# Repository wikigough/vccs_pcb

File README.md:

# Design
## Aims
 - The primary aim of this design was to make a tool for the lab for various testing purposes, which is why there are multiple current modes for the sink.
 - The secondary aim was to experiment with image printing on PCBs and learn how to use Inkscape!

## Design details
The design is a simple voltage controlled current sink. The simulation for the LTSpice circuit simualtion is stored in `\sims`. 
In a nutshell, the sink is controlled by applying 0-1V into the VCONTROL input, either into the SMA connector or the right angled header. 
The `SINK_SELECTx` setting maps the 0-1V voltage input to one of either: 0-3A, 0-1A, 0-100mA, 0-10mA or 0-1mA.
_For inductive loads, please control the slew rate into the VCONTROL input, or adjust the initial passive RC filter from the VCONTROL input, otherwise the control loop may oscillate._

### Image vs silkscreen
 Please note, although there is silkscreen in the KiCAD project, the silkscreen was not generated as a manufacturing output, and was only used as a guide for the image in inkscape. 
 Both silkscreen *and* image printing are allowed, where silkscreen can be applied after the image printing. In hindsight, this combination could've been used.  

### External Control
A right-angled header was put into the design, so that the circuit can be controlled by an external microcontroller. 

## Library
The parts used in the library are stored in a different repo. For passives, the approach of using generic parts and filling them into the schematic was taken. 

# Using the PCBA

## Sink select lines
*One* of the `SINK_SELECTx` lines must be set, either on the board with the onboard DIP switch or by applying voltage on the external header. Please ensure all the DIP switch is all off before plugging in an external controller! Please note that only *one* line is allowed to be set - otherwise you will parallelise sense resistors, unless that is what is wanted.

## Voltage control input
The sink is controlled by inputting a 0-1V voltage waveform into VCONTROL. The voltage can be arbitrary. 

## Fan
For higher power dissipations, a fan must be mounted against the PCB to cool the DPAK transistor, which is the main dissipator of power.

# Data generation and ordering
## Kicad output data generation
Although used PCBWay, used these settings for generating the data output:
https://jlcpcb.com/help/article/how-to-generate-gerber-and-drill-files-in-kicad-9
The size came out as correct in the order page.

## Instructions for ordering
The order screenshots are shown in `\vccs\pcbway_order`.
The png files uploaded are in `\vccs\art\final_images`.
The following guide was used: 
 - https://www.pcbway.com/blog/News/Unlock_Color_PCB_Printing_with_PCBWay_0939d559.html
 - https://www.pcbway.com/project/question/KiCAD_and_Multicolor_Silkscreen.html

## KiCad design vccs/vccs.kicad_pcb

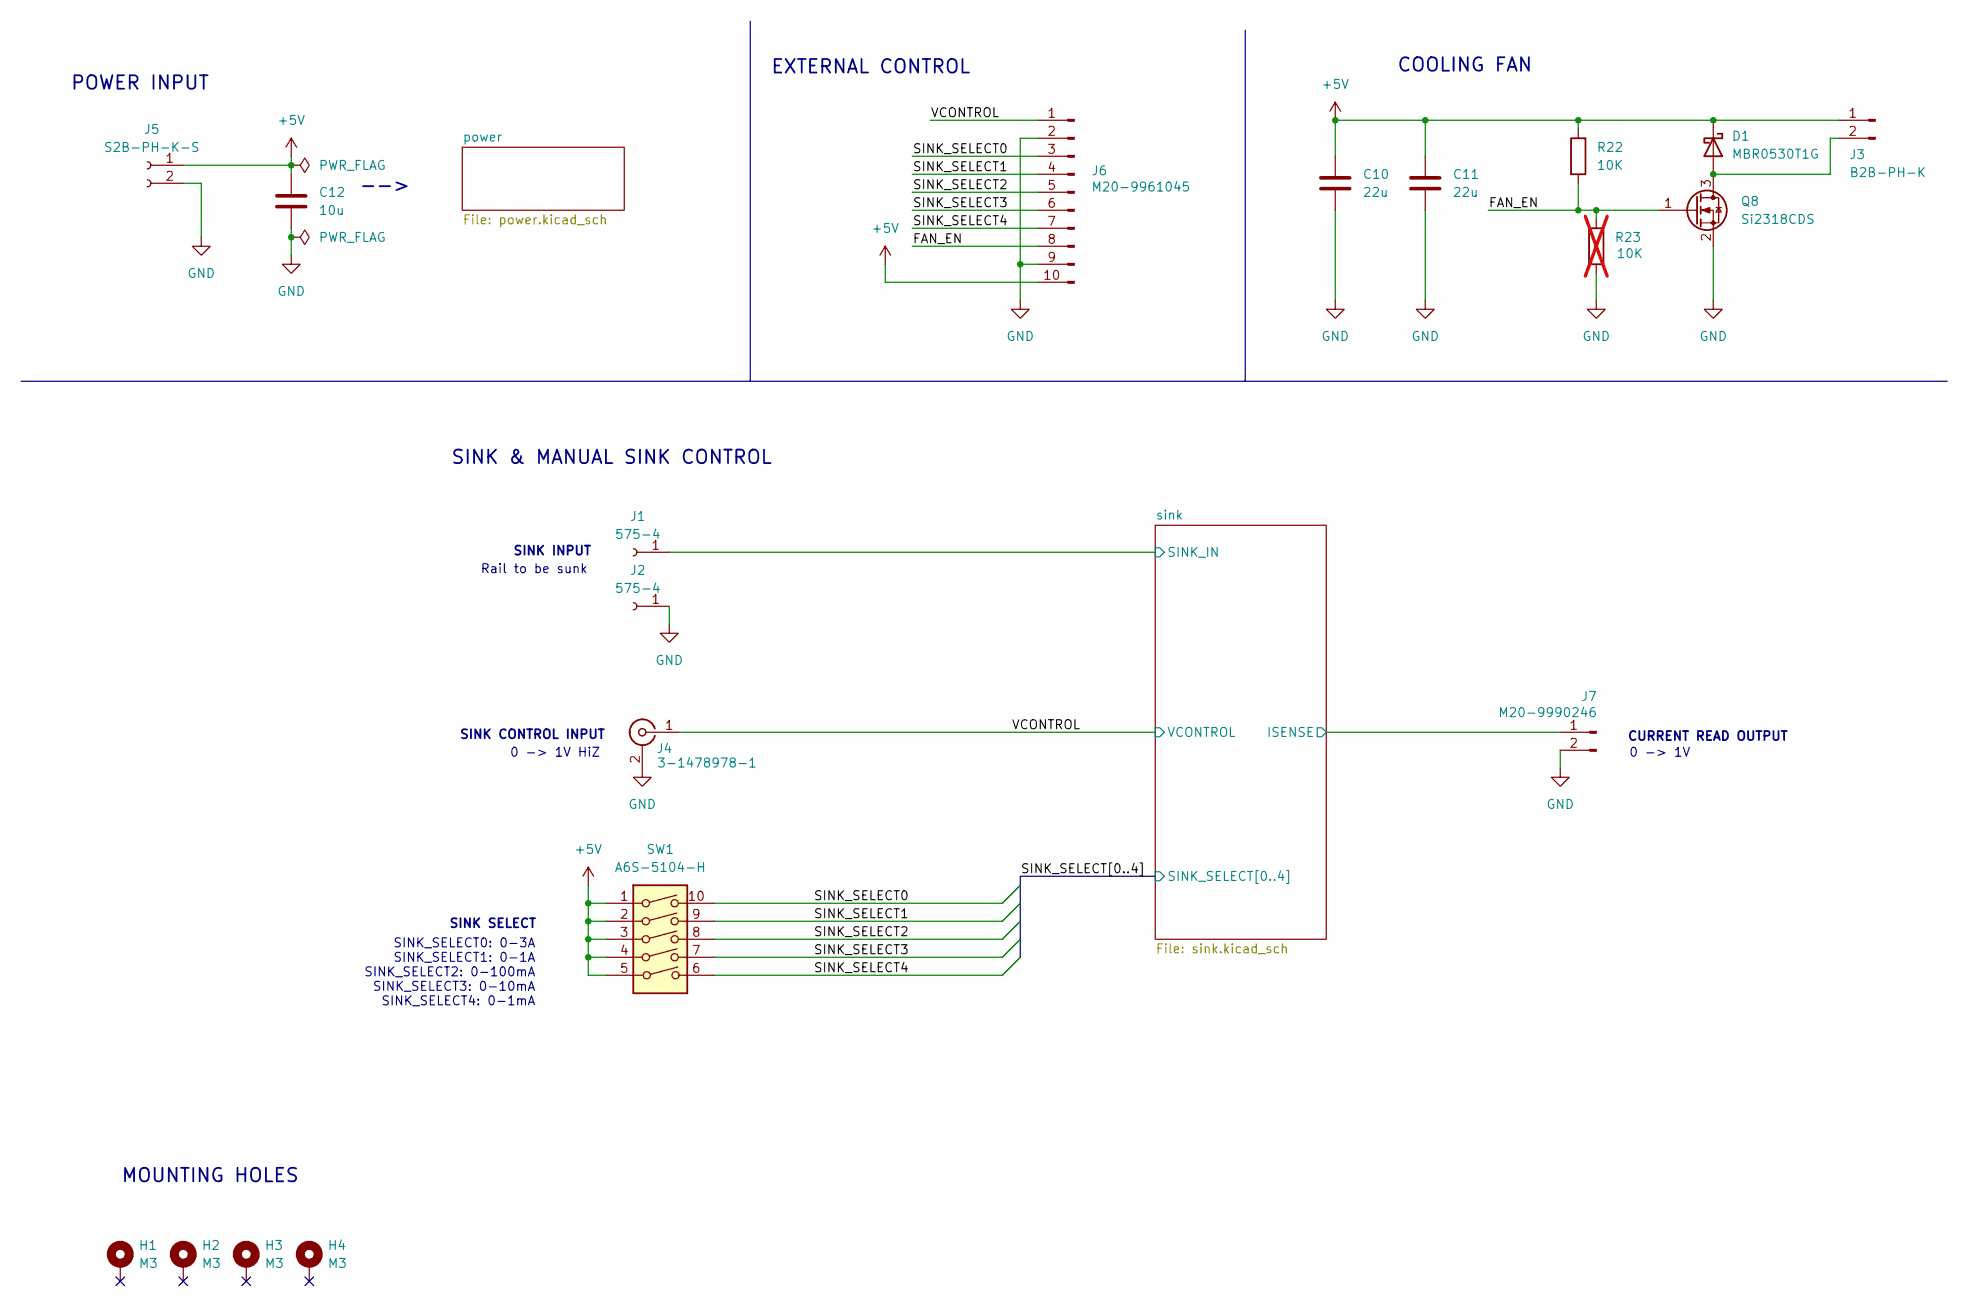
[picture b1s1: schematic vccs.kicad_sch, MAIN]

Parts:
C10, C11: 22u; C_1210_3225Metric_Pad1.33x2.70mm_HandSolder; Voltage Rating 16V; Tolerance 20%; MPN CL32A226MOJNNNE
C12: 10u; C_0805_2012Metric; Voltage Rating 16V; MPN GRM21BZ71C106KE15L
D1: MBR0530T1G; D_SOD-123; MPN MBR0530T1G
H1, H2, H3, H4: M3; MountingHole_3.2mm_M3_Pad_Via
J1, J2: 575-4; MPN 575-4
J3: B2B-PH-K; JST_PH_B2B-PH-K_1x02_P2.00mm_Vertical; MPN B2B-PH-K
J4: 3-1478978-1; MPN 3-1478978-1
J5: S2B-PH-K-S; JST_PH_S2B-PH-K_1x02_P2.00mm_Horizontal; MPN S2B-PH-K-S
J6: M20-9961045; PinHeader_1x10_P2.54mm_Horizontal; MPN M20-9961045
J7: M20-9990246; PinHeader_1x02_P2.54mm_Vertical; MPN M20-9990246
Q8: Si2318CDS; SOT-23-3; MPN SI2318CDS-T1-BE3
R22: 10K; R_0603_1608Metric; Tolerance 1%; Power Rating 1/10W; MPN RC0603FR-0710KL
R23: 10K; R_0603_1608Metric; Tolerance 1%; Power Rating 1/10W; MPN RC0603FR-0710KL; not fitted
SW1: A6S-5104-H; MPN A6S-5104-H

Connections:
+5V: C10.1, C11.1, C12.1, D1.1 (K), J3.1, J5.1, J6.10, R22.1, SW1.1, SW1.2, SW1.3, SW1.4, SW1.5; also elsewhere on the board
/FAN_EN: J6.8, Q8.1 (G), R22.2, R23.1
/SINK_SELECT0: J6.3, SW1.10; also elsewhere on the board
/SINK_SELECT1: J6.4, SW1.9; also elsewhere on the board
/SINK_SELECT2: J6.5, SW1.8; also elsewhere on the board
/SINK_SELECT3: J6.6, SW1.7; also elsewhere on the board
/SINK_SELECT4: J6.7, SW1.6; also elsewhere on the board
/VCONTROL: J4.1 (In), J6.1; also elsewhere on the board
/sink/ISENSE: J7.1; also elsewhere on the board
/sink/SINK_IN: J1.1; also elsewhere on the board
GND: C10.2, C11.2, C12.2, J2.1, J4.2 (Ext), J5.2, J6.2, J6.9, J7.2, Q8.2 (S), R23.2; also elsewhere on the board
unnamed: D1.2 (A), J3.2, Q8.3 (D)

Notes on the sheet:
Rail to be sunk
0 -> 1V HiZ
-->
SINK & MANUAL SINK CONTROL
0 -> 1V
EXTERNAL CONTROL
COOLING FAN
SINK_SELECT0: 0-3A SINK_SELECT1: 0-1A SINK_SELECT2: 0-100mA SINK_SELECT3: 0-10mA SINK_SELECT4: 0-1mA
CURRENT READ OUTPUT
SINK SELECT
SINK CONTROL INPUT
SINK INPUT
MOUNTING HOLES
POWER INPUT

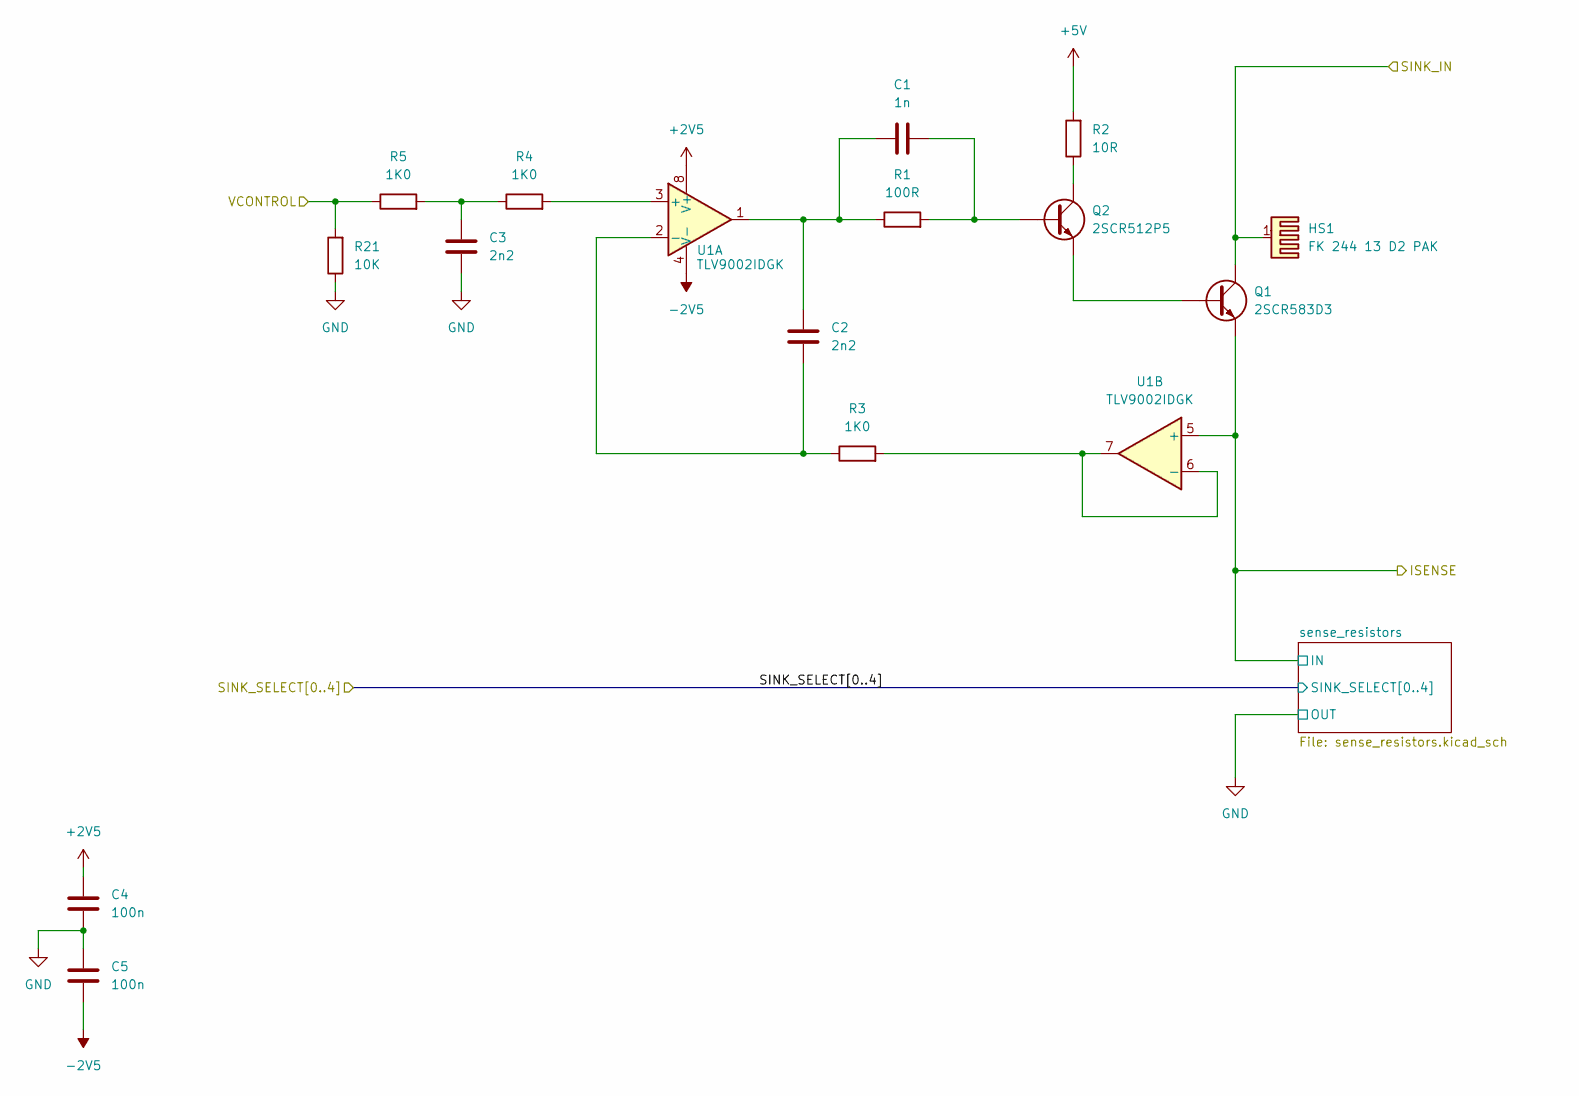
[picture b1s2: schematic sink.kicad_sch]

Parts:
C1: 1n; C_0603_1608Metric; Voltage Rating 50V; MPN GRM1885C1H102JA01D
C2, C3: 2n2; C_0603_1608Metric; Voltage Rating 50V; MPN GRM1885C1H222JA01D
C4, C5: 100n; C_0603_1608Metric; Voltage Rating 50V; MPN GCJ188R71H104KA12D
HS1: FK 244 13 D2 PAK; MPN FK 244 13 D2 PAK
Q1: 2SCR583D3; TO-252-2; MPN 2SCR583D3
Q2: 2SCR512P5; SOT-89-3; MPN 2SCR512P5
R1: 100R; R_0603_1608Metric; Tolerance 1%; Power Rating 1/10W; MPN RC0603FR-07100RL
R2: 10R; R_0603_1608Metric; Tolerance 1%; Power Rating 1/10W; MPN RC0603FR-0710RL
R3, R4, R5: 1K0; R_0603_1608Metric; Tolerance 1%; Power Rating 1/10W; MPN RC0603FR-071KL
R21: 10K; R_0603_1608Metric; Tolerance 1%; Power Rating 1/10W; MPN RC0603FR-0710KL
U1: TLV9002IDGK; VSSOP-8_3x3mm_P0.65mm; MPN TLV9002IDGK

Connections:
+2V5: C4.2, U1.8 (V+); also elsewhere on the board
+5V: R2.2; also elsewhere on the board
-2V5: C5.1, U1.4 (V-); also elsewhere on the board
/VCONTROL: R5.1, R21.2; also elsewhere on the board
/sink/ISENSE: Q1.3 (E), U1.5 (+); also elsewhere on the board
/sink/SINK_IN: HS1.1, Q1.2 (C); also elsewhere on the board
GND: C3.1, C4.1, C5.2, R21.1; also elsewhere on the board
unnamed: C1.1, C2.2, R1.1, U1.1
unnamed: C3.2, R4.1, R5.2
unnamed: Q1.1 (B), Q2.3 (E)
unnamed: C1.2, Q2.1 (B), R1.2
unnamed: Q2.2 (C), R2.1
unnamed: R4.2, U1.3 (+)
unnamed: C2.1, R3.1, U1.2 (-)
unnamed: R3.2, U1.6 (-), U1.7

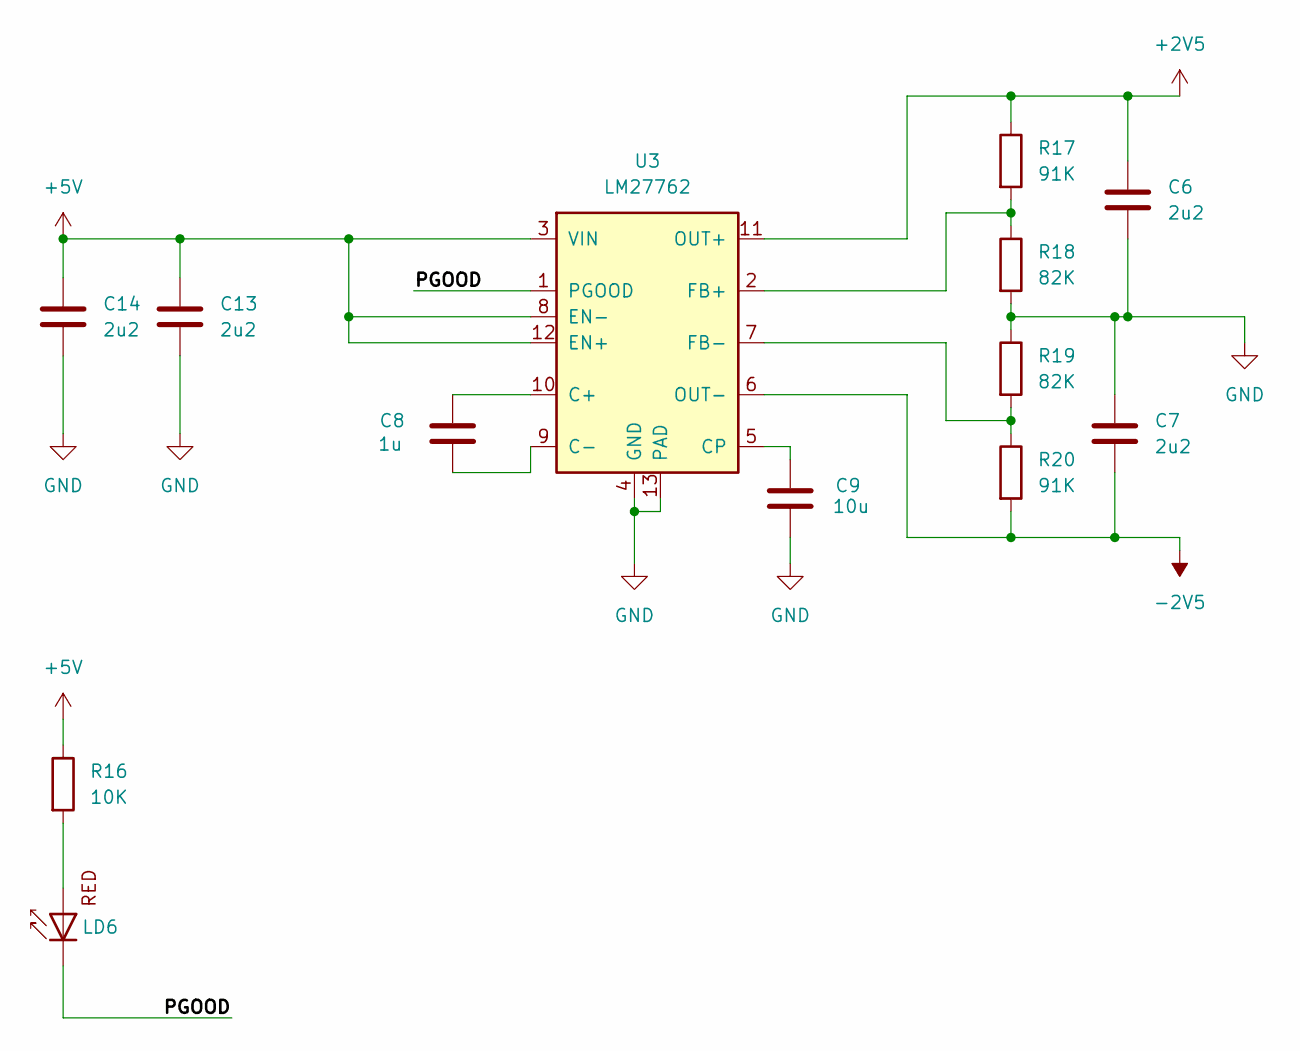
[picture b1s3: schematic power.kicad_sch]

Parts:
C6, C7, C13, C14: 2u2; C_0603_1608Metric; Voltage Rating 16V; MPN GRM188Z71C225KE43D
C8: 1u; C_0402_1005Metric; Voltage Rating 16V; MPN GRM155R61C105KA12D
C9: 10u; C_0603_1608Metric; Voltage Rating 16V; MPN GRM188R61C106MAALD
LD6: APHHS1005LSECK/J3-PF; LED_0402_1005Metric_Pad0.77x0.64mm_HandSolder; MPN APHHS1005LSECK/J3-PF
R16: 10K; R_0603_1608Metric; Tolerance 1%; Power Rating 1/10W; MPN RC0603FR-0710KL
R17, R20: 91K; R_0402_1005Metric; Tolerance 1%; Power Rating 1/16W; MPN RC0402FR-0791KL
R18, R19: 82K; R_0402_1005Metric; Tolerance 1%; Power Rating 1/16W; MPN RC0402FR-0782KL
U3: LM27762; WSON-12-1EP_3x2mm_P0.5mm_EP1x2.65; MPN LM27762DSS

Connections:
+2V5: C6.1, R17.1, U3.11 (OUT+); also elsewhere on the board
+5V: C13.1, C14.1, R16.1, U3.3 (VIN), U3.8 (EN-), U3.12 (EN+); also elsewhere on the board
-2V5: C7.2, R20.2, U3.6 (OUT-); also elsewhere on the board
/power/PGOOD: LD6.1 (K), U3.1 (PGOOD)
GND: C6.2, C7.1, C9.1, C13.2, C14.2, R18.2, R19.1, U3.4 (GND), U3.13 (PAD); also elsewhere on the board
unnamed: LD6.2 (A), R16.2
unnamed: C8.1, U3.10 (C+)
unnamed: C8.2, U3.9 (C-)
unnamed: C9.2, U3.5 (CP)
unnamed: R17.2, R18.1, U3.2 (FB+)
unnamed: R19.2, R20.1, U3.7 (FB-)

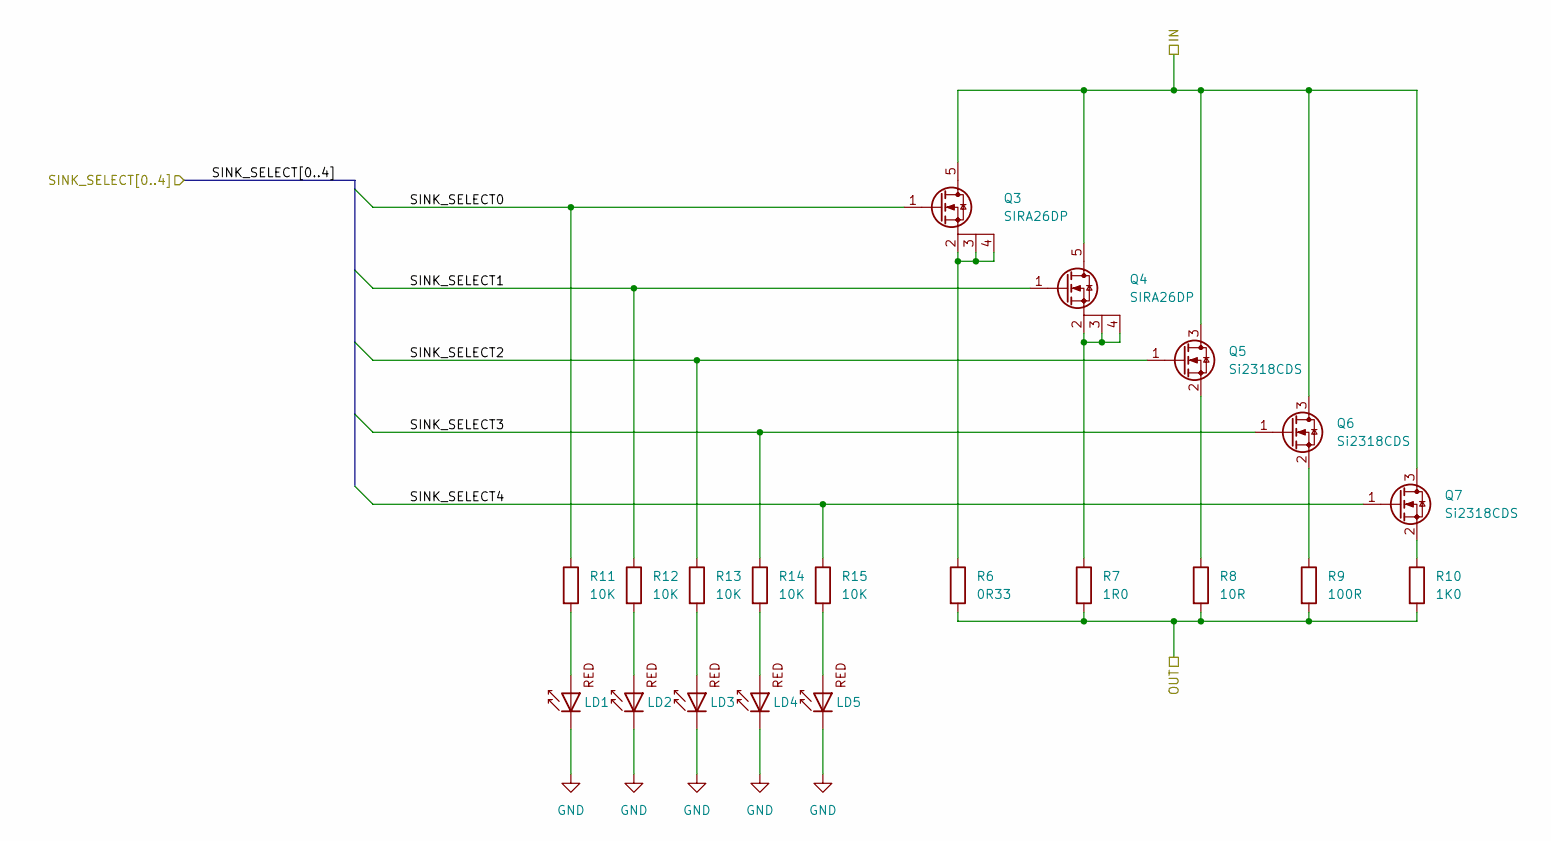
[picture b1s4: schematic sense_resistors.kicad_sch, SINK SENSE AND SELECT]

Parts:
LD1, LD2, LD3, LD4, LD5: APHHS1005LSECK/J3-PF; LED_0402_1005Metric_Pad0.77x0.64mm_HandSolder; MPN APHHS1005LSECK/J3-PF
Q3, Q4: SIRA26DP; PowerPAK_SO-8L_Single; MPN SIRA26DP-T1-RE3
Q5, Q6, Q7: Si2318CDS; SOT-23-3; MPN SI2318CDS-T1-BE3
R6: 0R33; R_1206_3216Metric; Tolerance 1%; Power Rating 1/4W; MPN RL1206FR-070R33L
R7: 1R0; R_1206_3216Metric; Tolerance 1%; Power Rating 1/4W; MPN RC1206FR-131RL
R8: 10R; R_1206_3216Metric; Tolerance 1%; Power Rating 1/4W; MPN RC1206FR-0710RL
R9: 100R; R_1206_3216Metric; Tolerance 1%; Power Rating 1/4W; MPN RC1206FR-07100RL
R10: 1K0; R_1206_3216Metric; Tolerance 1%; Power Rating 1/4W; MPN RC1206FR-071KL
R11, R12, R13, R14, R15: 10K; R_0603_1608Metric; Tolerance 1%; Power Rating 1/10W; MPN RC0603FR-0710KL

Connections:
/SINK_SELECT0: Q3.1 (G), R11.1; also elsewhere on the board
/SINK_SELECT1: Q4.1 (G), R12.1; also elsewhere on the board
/SINK_SELECT2: Q5.1 (G), R13.1; also elsewhere on the board
/SINK_SELECT3: Q6.1 (G), R14.1; also elsewhere on the board
/SINK_SELECT4: Q7.1 (G), R15.1; also elsewhere on the board
/sink/ISENSE: Q3.5 (D), Q4.5 (D), Q5.3 (D), Q6.3 (D), Q7.3 (D); also elsewhere on the board
GND: LD1.1 (K), LD2.1 (K), LD3.1 (K), LD4.1 (K), LD5.1 (K), R6.2, R7.2, R8.2, R9.2, R10.2; also elsewhere on the board
unnamed: LD1.2 (A), R11.2
unnamed: LD2.2 (A), R12.2
unnamed: LD3.2 (A), R13.2
unnamed: LD4.2 (A), R14.2
unnamed: LD5.2 (A), R15.2
unnamed: Q3.2 (S), Q3.3 (S), Q3.4 (S), R6.1
unnamed: Q4.2 (S), Q4.3 (S), Q4.4 (S), R7.1
unnamed: Q5.2 (S), R8.1
unnamed: Q6.2 (S), R9.1
unnamed: Q7.2 (S), R10.1

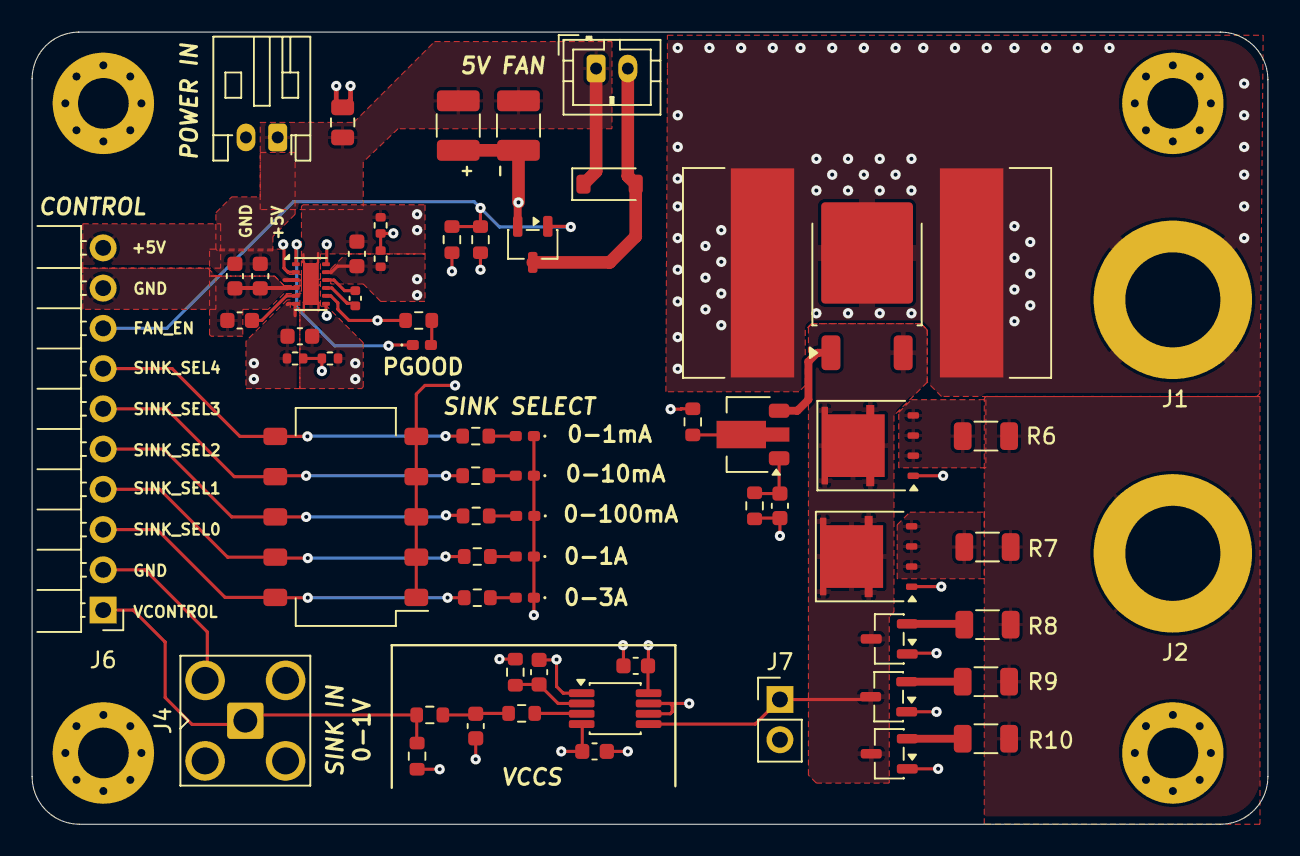
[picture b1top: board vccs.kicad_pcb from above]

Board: 4 copper layers, 78.0 x 50.0 mm, 67 parts (0 on the bottom side), 39 nets.

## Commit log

2026-01-18 first initial commit
    Added .gitignore for KiCad and LTSpice and added empty project files.
2026-01-18 Iterated sim and now putting into KiCad
2026-02-07 DRC pass
    Check in before adding artwork and double checking parts.
2026-02-08 A1 RELEASE
    A1 released - pending feedback from PCBWay
